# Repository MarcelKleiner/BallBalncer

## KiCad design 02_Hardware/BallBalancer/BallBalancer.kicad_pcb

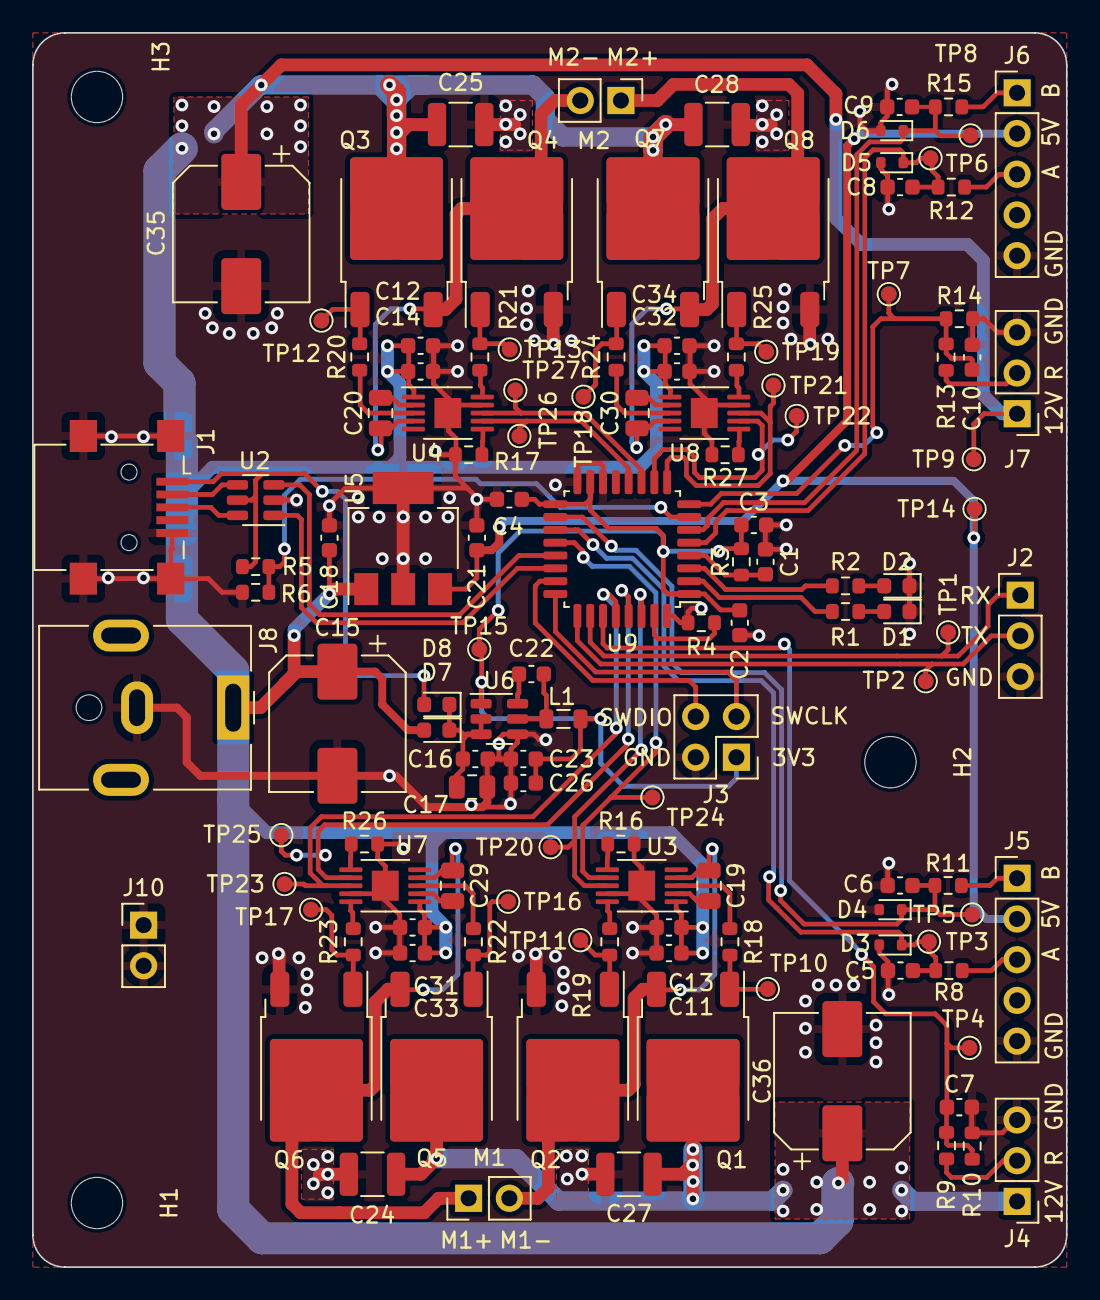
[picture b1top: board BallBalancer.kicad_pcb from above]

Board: 2 copper layers, 64.5 x 77.0 mm, 128 parts (0 on the bottom side), 71 nets.

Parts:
C1, C2, C3, C4, C7, C10, C13, C14, C16, C18, C21, C22, C31, C32: 100n; C_0603_1608Metric
C5, C6, C8, C9: 1n; C_0603_1608Metric
C11, C12, C33, C34: 1u; C_0603_1608Metric
C15, C35, C36: 330u; CP_Elec_8x10
C17: 10u; C_0805_2012Metric
C19, C20, C29, C30: 1000p; C_0805_2012Metric
C23, C26: 22u; C_0603_1608Metric
C24, C25, C27, C28: 10u; C_1210_3225Metric
D1: LED_R; LED_0603_1608Metric
D2: LED_G; LED_0603_1608Metric
D3, D4, D5, D6: MM5Z3V3; D_SOD-523
D7, D8: SD0603; D_0603_1608Metric
H1, H2, H3: MountingHole; MountingHole_3.2mm_M3
J1: USB_B_Micro; USB_Mini-B_Lumberg_2486_01_Horizontal
J2: Raspberry PI UART; PinHeader_1x03_P2.54mm_Vertical
J3: SWD; PinHeader_2x02_P2.54mm_Vertical
J4: Reference switch 1; PinHeader_1x03_P2.54mm_Vertical
J5: ENCODER 1; PinHeader_1x05_P2.54mm_Vertical
J6: ENCODER 2; PinHeader_1x05_P2.54mm_Vertical
J7: Reference switch 2; PinHeader_1x03_P2.54mm_Vertical
J8: Jack-DC; BarrelJack_CUI_PJ-063AH_Horizontal
J10: GND; PinHeader_1x02_P2.54mm_Vertical
L1: 3.3u; L_0805_2012Metric
M1, M2: Motor_DC; PinHeader_1x02_P2.54mm_Vertical
Q1, Q2, Q3, Q4, Q5, Q6, Q7, Q8: DMN10H220L; TO-252-2
R1, R2: 240; R_0603_1608Metric
R3, R4: 100k; R_0603_1608Metric
R5, R8, R11, R12, R15, R16, R17, R26, R27: 10k; R_0603_1608Metric
R6: 15k; R_0603_1608Metric
R9, R13: 3.3k; R_0603_1608Metric
R10, R14: 1k; R_0603_1608Metric
R18, R19, R20, R21, R22, R23, R24, R25: 22; R_0603_1608Metric
TP1: UART_RX; TestPoint_Pad_D1.0mm
TP2: UART_TX; TestPoint_Pad_D1.0mm
TP3: ENCODER1_A; TestPoint_Pad_D1.0mm
TP4: REF_MOT1; TestPoint_Pad_D1.0mm
TP5: ENCODER1_B; TestPoint_Pad_D1.0mm
TP6: ENCODER2_A; TestPoint_Pad_D1.0mm
TP7: REF_MOT2; TestPoint_Pad_D1.0mm
TP8: ENCODER2_B; TestPoint_Pad_D1.0mm
TP9: 12V; TestPoint_Pad_D1.0mm
TP10: GH_CH1L; TestPoint_Pad_D1.0mm
TP11: GL_CH1L; TestPoint_Pad_D1.0mm
TP12: GH_CH2L; TestPoint_Pad_D1.0mm
TP13: GL_CH2L; TestPoint_Pad_D1.0mm
TP14: 5V; TestPoint_Pad_D1.0mm
TP15: 3.3V; TestPoint_Pad_D1.0mm
TP16: GH_CH1R; TestPoint_Pad_D1.0mm
TP17: GL_CH1R; TestPoint_Pad_D1.0mm
TP18: GH_CH2R; TestPoint_Pad_D1.0mm
TP19: GL_CH2R; TestPoint_Pad_D1.0mm
TP20, TP21, TP22, TP23, TP24, TP25, TP26, TP27: IN_CH2R; TestPoint_Pad_D1.0mm
U2: USBLC6-2SC6; SOT-23-6
U3, U4, U7, U8: DGD0506A; MSOP-10-1EP_3x3mm_P0.5mm_EP1.68x1.88mm
U5: LM2937IMP5; SOT-223-3_TabPin2
U6: AP63203WU; TSOT-23-6
U9: STM32G431K8Tx; LQFP-32_7x7mm_P0.8mm

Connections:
+3V3: C2.2, C3.2, C4.2, C23.2, C26.2, J3.1, L1.2, R3.1, TP15.1, U6.1 (FB), U9.1 (VDD), U9.15 (VDDA), U9.17 (VDD)
+5V: C21.1, J5.2, J6.2, TP14.1, U5.3 (VO)
+12V: C11.2, C12.2, C13.2, C14.2, C15.1, C18.1, C24.2, C25.2, C27.2, C28.2, C31.2, C32.2, C33.2, C34.2, C35.1, C36.1, D7.2 (A), J4.1, J7.1, J8.1, Q1.2 (D), Q3.2 (D), Q5.2 (D), Q7.2 (D), TP9.1, U3.1 (Vcc), U4.1 (Vcc), U5.1 (VI), U7.1 (Vcc), U8.1 (Vcc)
+12VA: C16.1, C17.1, D7.1 (K), D8.1 (K), U6.2 (EN), U6.3 (IN)
/Main/D+: J1.3 (D+), U2.6 (I/O1)
/Main/D-: J1.2 (D-), U2.4 (I/O2)
/Main/ENCODER1_A: C5.1, D3.1 (K), R8.2, TP3.1, U9.19 (PA9)
/Main/ENCODER1_A_OUT: J5.3, R8.1
/Main/ENCODER1_B: C6.1, D4.1 (K), R11.2, TP5.1, U9.18 (PA8)
/Main/ENCODER1_B_OUT: J5.1, R11.1
/Main/ENCODER2_A: C8.1, D5.1 (K), R12.2, TP6.1, U9.5 (PA0)
/Main/ENCODER2_A_OUT: J6.3, R12.1
/Main/ENCODER2_B: C9.1, D6.1 (K), R15.2, TP8.1, U9.6 (PA1)
/Main/ENCODER2_B_OUT: J6.1, R15.1
/Main/LED1: R1.1, U9.2 (PF0)
/Main/LED2: R2.1, U9.3 (PF1)
/Main/REF_MOT1: C7.1, R9.2, R10.1, TP4.1, U9.27 (PB4)
/Main/REF_MOT2: C10.1, R13.2, R14.1, TP7.1, U9.8 (PA3)
/Main/RSPI_RX: J2.2, TP2.1, U9.25 (PA15)
/Main/RSPI_TX: J2.1, TP1.1, U9.26 (PB3)
/Main/SWCLK: J3.3, U9.24 (PA14)
/Main/SWDIO: J3.4, U9.23 (PA13)
/Main/USB_DM: U2.3 (I/O2), U9.21 (PA11)
/Main/USB_DP: U2.1 (I/O1), U9.22 (PA12)
/Main/VUSB: R5.2, R6.2, U9.7 (PA2)
EN_MOT_CH1L: TP24.1, U3.7 (EN), U9.20 (PA10)
EN_MOT_CH1R: TP25.1, U7.7 (EN), U9.29 (PB6)
EN_MOT_CH2L: TP26.1, U4.7 (EN), U9.12 (PA7)
EN_MOT_CH2R: TP22.1, U8.7 (EN), U9.10 (PA5)
GND: C1.1, C2.1, C3.1, C4.1, C5.2, C6.2, C7.2, C8.2, C9.2, C10.2, C11.1, C12.1, C13.1, C14.1, C15.2, C16.2, C17.2, C18.2, C21.2, C23.1, C24.1, C25.1, C26.1, C27.1, C28.1, C31.1, C32.1, C33.1, C34.1, C35.2, C36.2, D1.1 (K), D2.1 (K), D3.2 (A), D4.2 (A), D5.2 (A), D6.2 (A), J1.5 (GND), J1.6 (Shield), J2.3, J3.2, J4.3, J5.5, J6.5, J7.3, J8.2, J10.1, J10.2, Q2.3 (S), Q4.3 (S), Q6.3 (S), Q8.3 (S), R4.1, R6.1, R10.2, R14.2, R16.2, R17.2, R26.2, R27.2, U2.2 (GND), U3.9 (COM), U3.11 (PAD), U4.9 (COM), U4.11 (PAD), U5.2 (GND), U6.4 (GND), U7.9 (COM), U7.11 (PAD), U8.9 (COM), U8.11 (PAD), U9.14 (VSSA), U9.16 (VSS), U9.32 (VSS)
IN_MOT_CH1L: TP20.1, U3.8 (IN), U9.30 (PB7)
IN_MOT_CH1R: TP23.1, U7.8 (IN), U9.28 (PB5)
IN_MOT_CH2L: TP27.1, U4.8 (IN), U9.11 (PA6)
IN_MOT_CH2R: TP21.1, U8.8 (IN), U9.9 (PA4)
unnamed: D1.2 (A), R1.2
unnamed: D2.2 (A), R2.2
unnamed: J4.2, R9.1
unnamed: J7.2, R13.1
unnamed: C29.1, M1.1 (+), Q5.3 (S), Q6.2 (D), U7.4 (Vs)
unnamed: C19.1, M1.2 (-), Q1.3 (S), Q2.2 (D), U3.4 (Vs)
unnamed: C30.1, M2.1 (+), Q7.3 (S), Q8.2 (D), U8.4 (Vs)
unnamed: C20.1, M2.2 (-), Q3.3 (S), Q4.2 (D), U4.4 (Vs)
unnamed: Q1.1 (G), R18.1, TP10.1
unnamed: Q2.1 (G), R19.2, TP11.1
unnamed: Q3.1 (G), R20.1, TP12.1
unnamed: Q4.1 (G), R21.2, TP13.1
unnamed: Q5.1 (G), R22.1, TP16.1
unnamed: Q6.1 (G), R23.2, TP17.1
unnamed: Q7.1 (G), R24.1, TP18.1
unnamed: Q8.1 (G), R25.2, TP19.1
unnamed: R16.1, U3.6 (DT)
unnamed: R18.2, U3.3 (HO)
unnamed: R19.1, U3.10 (LO)
unnamed: C19.2, U3.2 (VB)
unnamed: R17.1, U4.6 (DT)
unnamed: R20.2, U4.3 (HO)
unnamed: R21.1, U4.10 (LO)
unnamed: C20.2, U4.2 (VB)
unnamed: C22.2, U6.6 (BST)
unnamed: C22.1, L1.1, U6.5 (SW)
unnamed: R26.1, U7.6 (DT)
unnamed: R22.2, U7.3 (HO)
unnamed: R23.1, U7.10 (LO)
unnamed: C29.2, U7.2 (VB)
unnamed: R27.1, U8.6 (DT)
unnamed: R24.2, U8.3 (HO)
unnamed: R25.1, U8.10 (LO)
unnamed: C30.2, U8.2 (VB)
unnamed: R4.2, U9.31 (PB8)
unnamed: C1.2, R3.2, U9.4 (PG10)
VBUS: D8.2 (A), J1.1 (VBUS), R5.1, U2.5 (VBUS)

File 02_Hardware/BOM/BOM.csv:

Item,"Qty","Reference(s)","Value","LibPart","Footprint","Datasheet","DNP","Hersteller Nr.","Info","Mouser Nr."				
1,"14","C1, C2, C3, C4, C7, C10, C13, C14, C16, C18, C21, C22, C31, C32","100n","Device:C","Capacitor_SMD:C_0603_1608Metric","https://www.mouser.ch/datasheet/2/585/MLCC-1837944.pdf","","885382206004","0.1uF	 50V, X7R	 -55C	+125C","710-885382206004"	
2,"4","C5, C6, C8, C9","1n","Device:C","Capacitor_SMD:C_0603_1608Metric","https://www.mouser.ch/datasheet/2/40/C0GNP0_Dielectric-951274.pdf","","06035C102KAT2A","1nF	 50V	 X7R	 -55C	+125C","581-06035C102K"
3,"4","C11, C12, C33, C34","1u","Device:C","Capacitor_SMD:C_0603_1608Metric","~","","CL10B105KA8NNNC","1uF	 25V	X7R	 -55C	+125C","187-CL10B105KA8NNNC"
4,"3","C15, C35, C36","330u","Device:C_Polarized","Capacitor_SMD:CP_Elec_8x10","~","","UWT1E331MNL1GS","330uF	 25V	 -55C	 +105C	 ALU","647-UWT1E331MNL1S"
5,"1","C17","10u","Device:C","Capacitor_SMD:C_0805_2012Metric","~","","C2012X5R1V106K085AC","10uF	 35V	 X5R	 -55C	 +85C","810-C2012X5R1V106K0C"
6,"4","C19, C20, C29, C30","1000p","Device:C","Capacitor_SMD:C_0805_2012Metric","~","","C0805J102K5RACAUTO","1000pF	 50V	 X7R	 -55C	 +125C","80-C0805J102K5RAUTO"
7,"2","C23, C26","22u","Device:C","Capacitor_SMD:C_0603_1608Metric","~","","CL10A226MO7JZNC","22uF	 16V	 X5R	 -55C	 +85C","187-CL10A226MO7JZNC"
8,"4","C24, C25, C27, C28","10u","Device:C","Capacitor_SMD:C_1210_3225Metric","~","","CL32B106KMVNNWE","10uF	 63V	 X7R	 -55C	 +125C","187-CL32B106KMVNNWE"
9,"1","D1","LED_R","Device:LED","LED_SMD:LED_0603_1608Metric","~","","150060RS75000","Red	 20mA	 2V","710-150060RS75000"		
10,"1","D2","LED_G","Device:LED","LED_SMD:LED_0603_1608Metric","~","","150060VS75000","Green	 20mA	 2V","710-150060VS75000"		
11,"4","D3, D4, D5, D6","MM5Z3V3","Device:D_Zener","Diode_SMD:D_SOD-523","https://www.mouser.ch/datasheet/2/308/MM5Z2V4T1-D-108556.pdf","","MM5Z3V3T1G","3.3V	 500mW ","863-MM5Z3V3T1G"			
12,"2","D7, D8","SD0603","Device:D_Schottky","Diode_SMD:D_0603_1608Metric","https://www.mouser.ch/datasheet/2/40/schottky-776407.pdf","","SD0603S040S0R2","200mA	 450mV","581-SD0603S040S0R2"			
13,"1","J1","USB_B_Micro","Connector:USB_B_Micro","Connector_USB:USB_Mini-B_Lumberg_2486_01_Horizontal","~","","UJ2-MBH-1-SMT-TR","USB Mini B","490-UJ2-MBH-1-SMT"				
14,"1","J2","Raspberry PI UART","Connector:Conn_01x03_Pin","Connector_PinHeader_2.54mm:PinHeader_1x03_P2.54mm_Vertical","~","","","",""				
15,"1","J3","SWD",":Conn_02x02_Counter_Clockwise_1","Connector_PinHeader_2.54mm:PinHeader_2x02_P2.54mm_Vertical","~","","","",""				
16,"1","J4","Reference switch 1","Connector:Conn_01x03_Pin","Connector_PinHeader_2.54mm:PinHeader_1x03_P2.54mm_Vertical","~","","","",""				
17,"1","J5","ENCODER 1","Connector:Conn_01x05_Pin","Connector_PinHeader_2.54mm:PinHeader_1x05_P2.54mm_Vertical","~","","","Connector for AMT102 Encoder (AMT102-V)",""				
18,"1","J6","ENCODER 2","Connector:Conn_01x05_Pin","Connector_PinHeader_2.54mm:PinHeader_1x05_P2.54mm_Vertical","~","","","Connector for AMT102 Encoder (AMT102-V)",""				
19,"1","J7","Reference switch 2","Connector:Conn_01x03_Pin","Connector_PinHeader_2.54mm:PinHeader_1x03_P2.54mm_Vertical","~","","","",""				
20,"1","J8","Jack-DC","Connector:Jack-DC","Connector_BarrelJack:BarrelJack_CUI_PJ-063AH_Horizontal","~","","","",""				
21,"1","L1","3.3u","Device:L","Inductor_SMD:L_0805_2012Metric","~","","IMC0805ER3R3J01","3.3uH	 800mA	 80mOhms","70-IMC0805ER3R3J01"		
22,"2","M1, M2","Motor_DC","Motor:Motor_DC","Connector_PinHeader_2.54mm:PinHeader_1x02_P2.54mm_Vertical","~","","","",""				
23,"8","Q1, Q2, Q3, Q4, Q5, Q6, Q7, Q8","DMN10H220L","Device:Q_NMOS_GDS","Package_TO_SOT_SMD:TO-252-2","~","","DMN10H220LK3-13","N-Channel	 100V	 7.5A	 220mOhms","621-DMN10H220LK3-13"	
24,"2","R1, R2","240","Device:R","Resistor_SMD:R_0603_1608Metric","~","","RC0603FR-13240RL","75V	1%	 100mW	 -55C	 +155C","603-RC0603FR-13240RL"
25,"2","R3, R4","100k","Device:R","Resistor_SMD:R_0603_1608Metric","~","","CRCW0603100KFKEAC","75V	1%	 100mW	 -55C	 +155C","71-CRCW0603100KFKEAC"
26,"9","R5, R8, R11, R12, R15, R16, R17, R26, R27","10k","Device:R","Resistor_SMD:R_0603_1608Metric","~","","CRCW060310K0FKEAC","75V	1%	 100mW	 -55C	 +155C","71-CRCW060310K0FKEAC"
27,"1","R6","15k","Device:R","Resistor_SMD:R_0603_1608Metric","~","","ERJ-3EKF1502V","75V	1%	 100mW	 -55C	 +155C","667-ERJ-3EKF1502V"
28,"1","R7","1.5k","Device:R","Resistor_SMD:R_0603_1608Metric","~","","CRCW06031K50JNEAC","75V	5%	 100mW	 -55C	 +155C","71-CRCW06031K50JNEAC"
29,"2","R9, R13","3.3k","Device:R","Resistor_SMD:R_0603_1608Metric","~","","ERJ-PB3B3301V","75V	0.10%	 200mW	 -55C	 +155C","667-ERJ-PB3B3301V"
30,"2","R10, R14","1k","Device:R","Resistor_SMD:R_0603_1608Metric","~","","CRCW06031K00FKEAC","75V	1%	 100mW	 -55C	 +155C","71-CRCW06031K00FKEAC"
31,"8","R18, R19, R20, R21, R22, R23, R24, R25","120","Device:R","Resistor_SMD:R_0603_1608Metric","~","","CRCW0603120RFKEAC","75V	1%	 100mW	 -55C	 +155C","71-CRCW0603120RFKEA"
32,"1","TP1","UART_RX","Connector:TestPoint","TestPoint:TestPoint_Pad_D1.0mm","~","","","",""				
33,"1","TP2","UART_TX","Connector:TestPoint","TestPoint:TestPoint_Pad_D1.0mm","~","","","",""				
34,"1","TP3","ENCODER1_A","Connector:TestPoint","TestPoint:TestPoint_Pad_D1.0mm","~","","","",""				
35,"1","TP4","REF_MOT1","Connector:TestPoint","TestPoint:TestPoint_Pad_D1.0mm","~","","","",""				
36,"1","TP5","ENCODER1_B","Connector:TestPoint","TestPoint:TestPoint_Pad_D1.0mm","~","","","",""				
37,"1","TP6","ENCODER2_A","Connector:TestPoint","TestPoint:TestPoint_Pad_D1.0mm","~","","","",""				
38,"1","TP7","REF_MOT2","Connector:TestPoint","TestPoint:TestPoint_Pad_D1.0mm","~","","","",""				
39,"1","TP8","ENCODER2_B","Connector:TestPoint","TestPoint:TestPoint_Pad_D1.0mm","~","","","",""				
40,"1","TP9","12V","Connector:TestPoint","TestPoint:TestPoint_Pad_D1.0mm","~","","","",""				
41,"1","TP10","GH_CH1L","Connector:TestPoint","TestPoint:TestPoint_Pad_D1.0mm","~","","","",""				
42,"1","TP11","GL_CH1L","Connector:TestPoint","TestPoint:TestPoint_Pad_D1.0mm","~","","","",""				
43,"1","TP12","GH_CH2L","Connector:TestPoint","TestPoint:TestPoint_Pad_D1.0mm","~","","","",""				
44,"1","TP13","GL_CH2L","Connector:TestPoint","TestPoint:TestPoint_Pad_D1.0mm","~","","","",""				
45,"1","TP14","5V","Connector:TestPoint","TestPoint:TestPoint_Pad_D1.0mm","~","","","",""				
46,"1","TP15","3.3V","Connector:TestPoint","TestPoint:TestPoint_Pad_D1.0mm","~","","","",""				
47,"1","TP16","GH_CH1R","Connector:TestPoint","TestPoint:TestPoint_Pad_D1.0mm","~","","","",""				
48,"1","TP17","GL_CH1R","Connector:TestPoint","TestPoint:TestPoint_Pad_D1.0mm","~","","","",""				
49,"1","TP18","GH_CH2R","Connector:TestPoint","TestPoint:TestPoint_Pad_D1.0mm","~","","","",""				
50,"1","TP19","GL_CH2R","Connector:TestPoint","TestPoint:TestPoint_Pad_D1.0mm","~","","","",""				
51,"8","TP20, TP21, TP22, TP23, TP24, TP25, TP26, TP27","IN_CH2R","Connector:TestPoint","TestPoint:TestPoint_Pad_D1.0mm","~","","","",""				
52,"1","U1","STM32L412K8Tx","MCU_ST_STM32L4:STM32L412K8Tx","Package_QFP:LQFP-32_7x7mm_P0.8mm","https://www.st.com/resource/en/datasheet/stm32l412k8.pdf","","STM32L412K8T6","80MHz	 40kB RAM	 64 kB Flash","511-STM32L412K8T6"		
53,"1","U2","USBLC6-2SC6","Power_Protection:USBLC6-2SC6","Package_TO_SOT_SMD:SOT-23-6","https://www.st.com/resource/en/datasheet/usblc6-2.pdf","","USBLC6-2SC6","USB TVS","511-USBLC6-2SC6"				
54,"4","U3, U4, U7, U8","DGD0506A","MK_Driver:DGD0506A","Package_SO:MSOP-10-1EP_3x3mm_P0.5mm_EP1.68x1.88mm","","","DGD0506AM10-13","","621-DGD0506AM10-13"				
55,"1","U5","LM2937IMP5","Regulator_Linear:LM2937xMP","Package_TO_SOT_SMD:SOT-223-3_TabPin2","http://www.ti.com/lit/ds/symlink/lm2937.pdf","","LM2937IMP-5.0/NOPB","5V LDO","926-LM2937IMP5.0NOPB"				
56,"1","U6","AP63203WU","Regulator_Switching:AP63203WU","Package_TO_SOT_SMD:TSOT-23-6","https://www.diodes.com/assets/Datasheets/AP63200-AP63201-AP6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","","AP63203WU-7","3.3V Buck Converter","621-AP63203WU-7"

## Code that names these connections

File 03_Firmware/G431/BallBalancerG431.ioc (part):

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Mcu.Name=STM32G431K(6-8-B)Tx
Mcu.Package=LQFP32
Mcu.UserName=STM32G431K8Tx
PA0.GPIOParameters=GPIO_Label
PA0.GPIO_Label=ENCODER2_A
PA0.Signal=S_TIM2_CH1
PA1.GPIOParameters=GPIO_Label
PA1.GPIO_Label=ENCODER2_B
PA1.Signal=S_TIM2_CH2
PA10.GPIOParameters=GPIO_Label
PA10.GPIO_Label=EN_MOT_CH1L
PA10.Signal=GPIO_Output
PA11.Mode=Device
PA11.Signal=USB_DM
PA12.Mode=Device
PA12.Signal=USB_DP
PA13.Mode=Serial_Wire
PA13.Signal=SYS_JTMS-SWDIO
PA14.Mode=Serial_Wire
PA14.Signal=SYS_JTCK-SWCLK
PA15.Mode=Asynchronous
PA15.Signal=USART2_RX
PA2.GPIOParameters=GPIO_Label
PA2.GPIO_Label=VUSB
PA2.Mode=IN3-Single-Ended
PA2.Signal=ADC1_IN3
PA3.GPIOParameters=GPIO_Label
PA3.GPIO_Label=REF_MOT2
PA3.Signal=GPIO_Input
PA4.GPIOParameters=GPIO_Label
PA4.GPIO_Label=IN_MOT_CH2R
PA4.Signal=S_TIM3_CH2
PA5.GPIOParameters=GPIO_Label
PA5.GPIO_Label=EN_MOT_CH2R
PA5.Signal=GPIO_Output
PA6.GPIOParameters=GPIO_Label
PA6.GPIO_Label=IN_MOT_CH2L
PA6.Signal=S_TIM3_CH1
PA7.GPIOParameters=GPIO_Label
PA7.GPIO_Label=EN_MOT_CH2L
PA7.Signal=GPIO_Output
PA8.GPIOParameters=GPIO_Label
PA8.GPIO_Label=ENCODER1_B
PA8.Signal=S_TIM1_CH1
PA9.GPIOParameters=GPIO_Label
PA9.GPIO_Label=ENCODER1_A
PA9.Signal=S_TIM1_CH2
PB3.Mode=Asynchronous
PB3.Signal=USART2_TX
PB4.GPIOParameters=GPIO_Label
PB4.GPIO_Label=REF_MOT1
PB4.Signal=GPIO_Input
PB5.GPIOParameters=GPIO_Label
PB5.GPIO_Label=IN_MOT_CH1R
PB5.Signal=S_TIM17_CH1
PB6.GPIOParameters=GPIO_Label
PB6.GPIO_Label=EN_MOT_CH1R
PB6.Signal=GPIO_Output
PB7.GPIOParameters=GPIO_Label
PB7.GPIO_Label=IN_MOT_CH1L
PB7.Signal=S_TIM3_CH4
PF0-OSC_IN.GPIOParameters=GPIO_Label
PF0-OSC_IN.GPIO_Label=LED1
PF0-OSC_IN.Signal=GPIO_Output
PF1-OSC_OUT.GPIOParameters=GPIO_Label
PF1-OSC_OUT.GPIO_Label=LED2
PF1-OSC_OUT.Signal=GPIO_Output
RCC.HSE_VALUE=8000000
RCC.SYSCLKFreq_VALUE=16000000
board=custom

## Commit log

2023-12-22 add gitignore and folderstructure
2023-12-23 add hardware
2023-12-23 Hardware schema and layout created
2023-12-23 ERC and DRC warnings and errors in schema and layout fixed
2023-12-25 Test points added and BOM created
2024-01-01 CAD files and hardware manufacturing data added
2024-02-11 update firmware, hardware and software
2024-02-11 motor1 left turn implemented
2024-02-17 replace microcontroller
2024-02-17 Layout completed with stm32g431
2024-02-29 update layout
2024-03-03 Firmware ported to G431 controller
2024-07-24 update controler
